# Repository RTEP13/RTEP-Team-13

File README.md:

#Real Time Spectrum Analyser

Audio Level Indicator and Spectrum Analyser for the Raspberry Pi (Zero).

The contents of this repository were part of a university project and is no longer being maintained. Further information on the project can be found in the wiki.

## Prerequisites
Install BCM 2835 Library
* [Latest version can be found from here](http://www.airspayce.com/mikem/bcm2835/)</br>
* [Version used for this project](http://www.airspayce.com/mikem/bcm2835/bcm2835-1.52.tar.gz) 
   After downloading to the pi, simply do the following from the pi's terminal
   ```
   tar zxvf bcm2835-1.52.tar.gz
   cd bcm2835-1.52
   ./configure
   make
   sudo make check
   sudo make install
   ```
* Ensure to install qt, qwt and other dependencies by entering the following commands into a terminal on the Pi:
```
$ sudo apt-get install qt4-dev-tools libqt4-dev qt4-qmake g++ make
$ sudo apt-get install libqwt-dev libqwt-doc libqwt6
$ sudo apt-get install xorg
```

## Introduction

The goal of this project is to provide a hardware and software solution for a real-time audio level indicator and spectrum analyser for the Raspberry Pi Zero.

The Raspberry Pi Zero can be configured as a USB virtual network gadget can can communicate to a PC through an SSH network connection. The user interface is provided making use of X forwarding using the X Windows System with the Pi Zero hosting the application.

The original idea for the project was unfortunately not completed due to hardware development and fabrication delays. The PCB was fabricated in China and the time required for fabrication and delivery meant that there was little time to write and test software for the platform.

The AD7705 ADC was used as a backup to demonstrate real time data acquisition using SPI and to demonstrate the QT spectrum analyser.

## Hardware requirements

* Raspberry Pi Zero configured as a USB virtual network gadget. See [this](http://blog.gbaman.info/?p=699) extremely helpful walkthrough.
 
## Software requirements

* [KiCad](http://kicad-pcb.org/) - Open source electronics design suite
* [Alsa](https://www.alsa-project.org/) - Provides audio functionality to the Pi
* [FFTW3](http://www.fftw.org/) - Software library for computing DFTs
* [QT](https://www.qt.io/) - Provides user experience

## Software build

To build:
```
$ git clone git@github.com:RTEP13/rtep-spectrum-analyser.git
$ cd rtep-spectrum-analyser/project/source/software/qt_interface
$ qmake
$ make
```
To run software from directory qt\_interface:
```
$ ./qtexample
```

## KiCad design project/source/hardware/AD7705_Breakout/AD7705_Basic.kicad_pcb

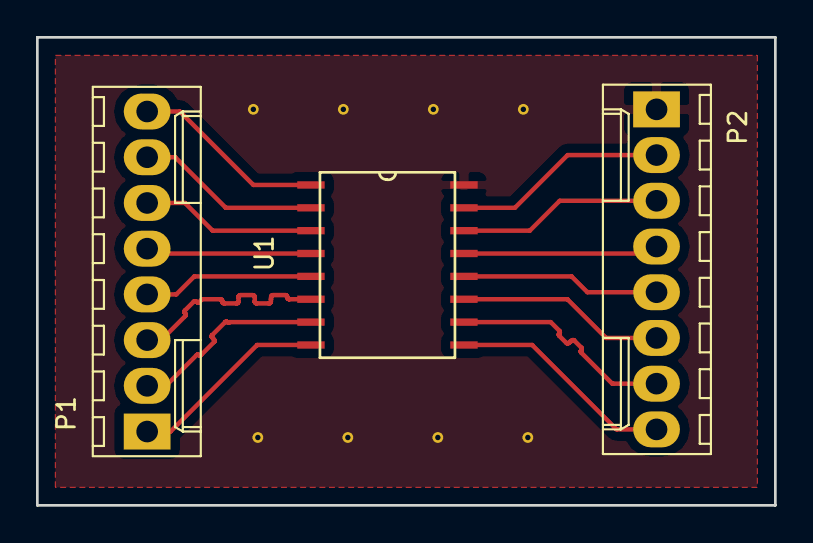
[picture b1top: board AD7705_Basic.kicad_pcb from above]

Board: 2 copper layers, 41.0 x 26.0 mm, 3 parts (0 on the bottom side), 16 nets.

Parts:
P1, P2: CONN_01X08; Molex_KK-6410-08_08x2.54mm_Straight
U1: AD7705

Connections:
unnamed: P1.1, U1.8
unnamed: P1.2, U1.7
unnamed: P1.3, U1.6
unnamed: P1.4, U1.5
unnamed: P1.5, U1.4
unnamed: P1.6, U1.3
unnamed: P1.7, U1.2
unnamed: P1.8, U1.1
unnamed: P2.1, U1.16
unnamed: P2.2, U1.15
unnamed: P2.3, U1.14
unnamed: P2.4, U1.13
unnamed: P2.5, U1.12
unnamed: P2.6, U1.11
unnamed: P2.7, U1.10
unnamed: P2.8, U1.9

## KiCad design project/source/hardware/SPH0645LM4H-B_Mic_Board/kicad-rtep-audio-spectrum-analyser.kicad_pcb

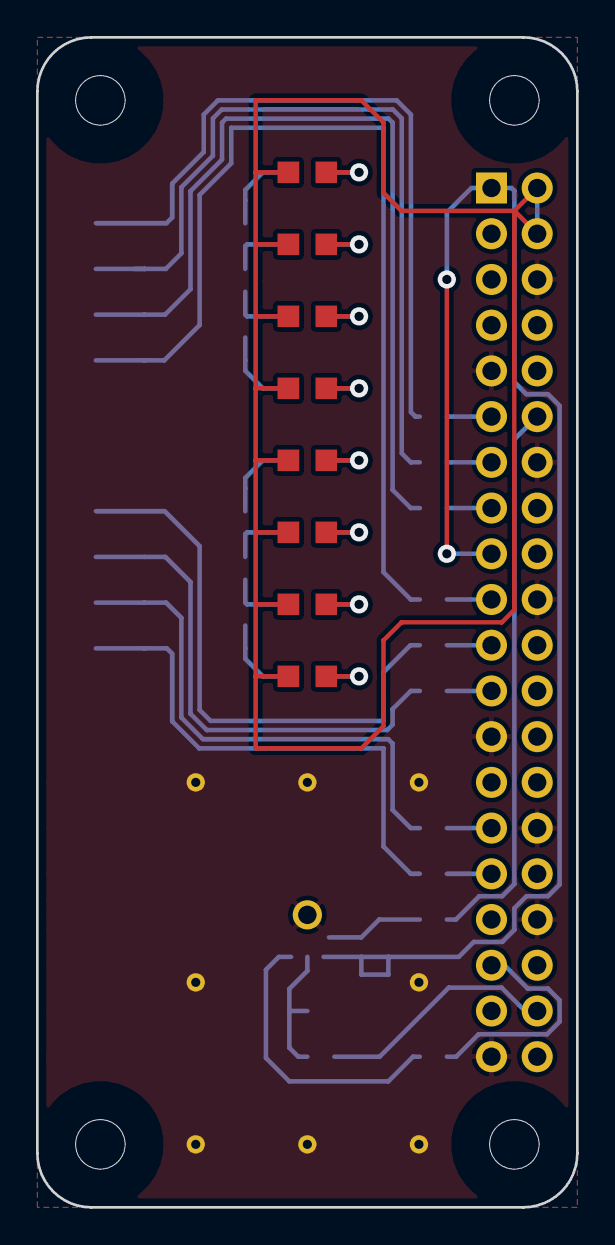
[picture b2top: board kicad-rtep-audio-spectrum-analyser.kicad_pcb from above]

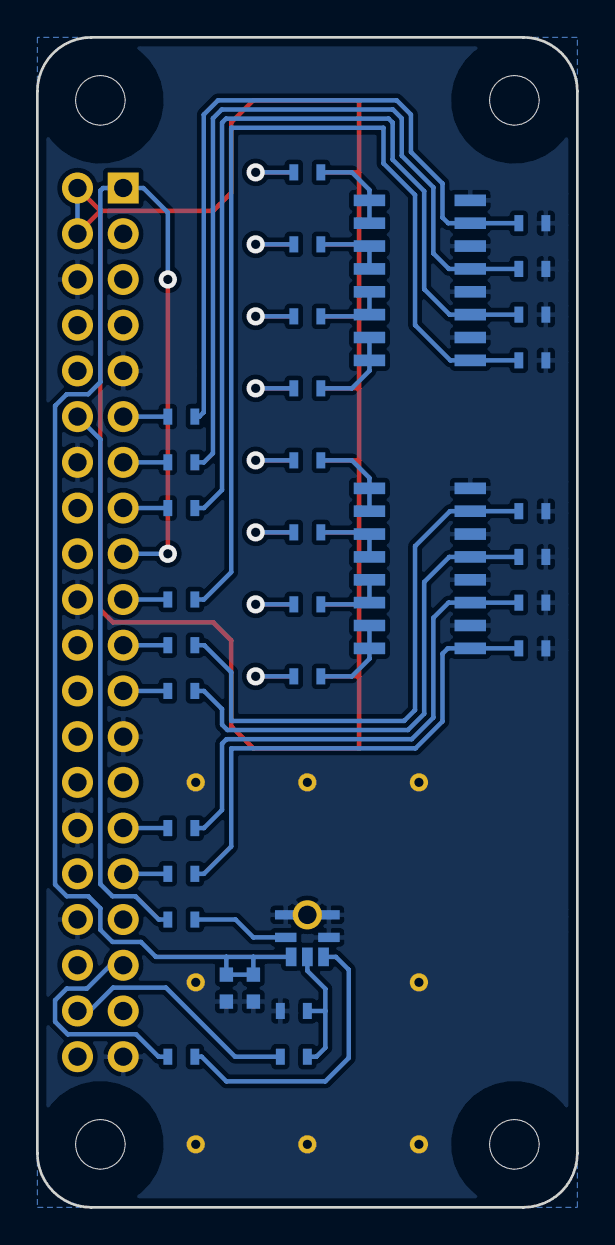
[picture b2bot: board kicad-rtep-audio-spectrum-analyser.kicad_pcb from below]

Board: 2 copper layers, 30.0 x 65.0 mm, 62 parts (33 on the bottom side), 41 nets.

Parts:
C1: 200pF; C-0603
C2: 0.1µF; C-0603
D1: LH-R974-LP-1; CHIPLED-0805
D2, D3: LY-R976-PS-36; CHIPLED-0805
D4, D5, D6, D7, D8: LG-R971-KN-1; CHIPLED-0805
MK1: SPH0645LM4H-B
MOUNTING-HOLE: MOUNTING-HOLE
MOUNTING-HOLE#2, MOUNTING-HOLE#3, MOUNTING-HOLE#4: MOUNTING-HOLE
P1: RASPBERRY PI GPIO; GPIO
Q1, Q2: MMPQ3904
R1, R4, R7, R10, R13, R16, R19, R22: 1kΩ; R-0603
R2, R5, R8, R11, R14, R17, R20, R23: 10kΩ; R-0603
R3, R6, R9, R12, R15, R18, R21, R24: 120Ω; R-0603
R25, R26, R27: 51Ω; R-0603
R28: 100kΩ; R-0603
STITCH: VAL**; STITCH
STITCH#2, STITCH#3, STITCH#4, STITCH#5, STITCH#6, STITCH#7, STITCH#8: VAL**; STITCH
VIAMASK: VAL**; VIAMASK
VIAMASK#2, VIAMASK#3, VIAMASK#4, VIAMASK#5, VIAMASK#6, VIAMASK#7, VIAMASK#8: VAL**; VIAMASK

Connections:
+3V3: C1.1, C2.1, MK1.VDD, P1.01, P1.17
+5V: D1.A, D2.A, D3.A, D4.A, D5.A, D6.A, D7.A, D8.A, P1.02, P1.04
/BCLK: MK1.BCLK, R25.1
/DATA: P1.38, R27.1
/LED1: P1.11, R1.1
/LED2: P1.13, R4.1
/LED3: P1.15, R7.1
/LED4: P1.19, R10.1
/LED5: P1.21, R13.1
/LED6: P1.23, R16.1
/LED7: P1.29, R19.1
/LED8: P1.31, R22.1
/WS: MK1.WS, R26.1
GND: C1.2, C2.2, MK1.GND, MK1.SEL, P1.06, P1.09, P1.14, P1.20, P1.25, P1.30, P1.34, P1.39, Q1.AE, Q1.BE, Q1.CE, Q1.DE, Q2.AE, Q2.BE, Q2.CE, Q2.DE, R2.1, R5.1, R8.1, R11.1, R14.1, R17.1, R20.1, R23.1, R28.1
unnamed: D1.C, R3.2
unnamed: D2.C, R6.2
unnamed: D3.C, R9.2
unnamed: D4.C, R12.2
unnamed: D5.C, R15.2
unnamed: D6.C, R18.2
unnamed: D7.C, R21.2
unnamed: D8.C, R24.2
unnamed: MK1.DATA, R27.2, R28.2
unnamed: P1.12, R25.2
unnamed: P1.35, R26.2
unnamed: Q1.AB, R1.2, R2.2
unnamed: Q1.AC1, Q1.AC2, R3.1
unnamed: Q1.BB, R4.2, R5.2
unnamed: Q1.BC1, Q1.BC2, R6.1
unnamed: Q1.CB, R7.2, R8.2
unnamed: Q1.CC1, Q1.CC2, R9.1
unnamed: Q1.DB, R10.2, R11.2
unnamed: Q1.DC1, Q1.DC2, R12.1
unnamed: Q2.AB, R13.2, R14.2
unnamed: Q2.AC1, Q2.AC2, R15.1
unnamed: Q2.BB, R16.2, R17.2
unnamed: Q2.BC1, Q2.BC2, R18.1
unnamed: Q2.CB, R19.2, R20.2
unnamed: Q2.CC1, Q2.CC2, R21.1
unnamed: Q2.DB, R22.2, R23.2
unnamed: Q2.DC1, Q2.DC2, R24.1

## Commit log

2017-03-16 Progress so far with ALSA & FFTW3 testing
    File sa.c is main dev code, progress is outlined in status.txt.
    Both playback and recorder have been combined into alsa_io.c with some audio files contained in folder too.
2017-03-16 Small update to status.txt
2017-03-30 First hardware revision complete
2017-04-07 Small tests for Alsa. Cleaning sa.c a bit
2017-04-07 README changes
2017-04-07 Spelling error in readme
2017-04-09 test commit, added MCP1525 datasheet
2017-04-09 added datasheets for suggested adc and I2s mems mic. also added a text document to store links
2017-04-10 demostrating pull request and fork
2017-04-11 README update
2017-04-11 Starting to add QT functionality
    Using the RTEP example QT program to get up and running. Added second plot for spectrum analysis and spinner button for increasing FFT samples.
    Next steps:
    - configure spectrum analysis plot for FFT.
    - create sound level meter
    - add ADC data aquisition
2017-04-12 Added new specanal class for calling fftw3. Moved around layout to fit our needs.
2017-04-12 Added axis titles, volume bar colour
2017-04-12 Merged FFTW3, works and shows a peak from sine wave.
    Took FFTW3 calls from alsa_tests and merged into QT code.
    Still to do:
    Use ring buffer instead of memmove for time data
    Provide user interaction for changing fft input & output size
    Possible reduction in FFT execution time with threads
2017-04-12 Adding control button methods
2017-04-13 Added a prerequisites section
    Added a prerequisites section with installation commands for qt qwt etc
2017-04-13 Correcting typo in ## header
2017-04-13 Correcting newline issue
2017-04-13 Small changes & getting it to work on linux pc
2017-04-14 Created new ring buffer class and started development
    Ring buffer class created, does not compile yet - fix these errors.
2017-04-14 first commit of the AD7705 demo
2017-04-15 updated comments on cpp and header files
2017-04-16 Ring buffer working, strange line
    Ring buffer approach now working but as Window::add(int val) method rather than as part of a class. Class approach was giving errors and using method was quicker to figure out.
    Strange line appearing as plot wraps round from the last input value to the first. Fix this.
2017-04-16 Added ADC class, stumbled with ring buffer
    Added ADC class for use with the AD7705 ADC, just needs code to work with input.
    Using a ring buffer with the QWT setSamples method is difficult to get correct as it reads out all data from data array startin fom element 0. A better solution required.
2017-04-16 License to thrill
2017-04-16 Beginning to merge ADC with QT work
2017-04-16 testing Markdown table of contents
2017-04-16 adding Schematic image
2017-04-16 added breakout schematics
2017-04-16 updating images in docs
2017-04-16 more images
2017-04-17 updating paths
2017-04-17 rpi2,3 pinout
2017-04-17 Merged ADC and Qt code. Now compiles correctly but exits when running due to lack of ADC comms.
2017-04-17 spi AD7705 pi connection image created and uploaded
2017-04-17 Update README.md
    Highlighted terminal instructions as inline
2017-04-17 updates to readme, .gitignore & tidying up
2017-04-17 Update README.md
    Updating link for image
2017-04-17 Fixed spi mode problem
2017-04-17 Fixed threading problems for ADC. Now launches correctly. Created script to run QwtExample after make
2017-04-17 Final commit
2017-08-20 Adding not maintained message
